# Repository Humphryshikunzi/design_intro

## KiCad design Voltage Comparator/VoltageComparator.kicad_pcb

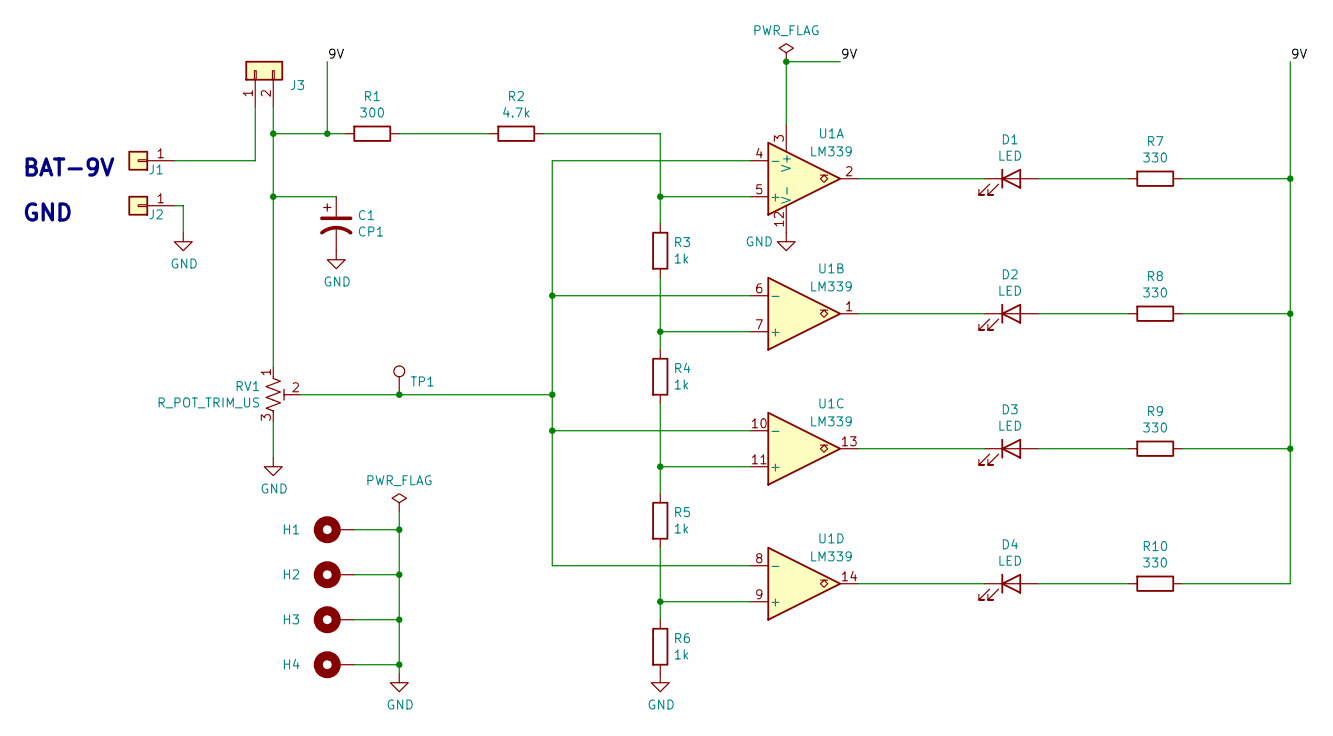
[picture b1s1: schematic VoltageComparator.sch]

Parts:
C1: CP1; CP_Radial_D10.0mm_P2.50mm
D1, D2, D3, D4: LED; LED_D3.0mm
H1, H2, H3, H4: MountingHole_Pad; MountingHole_2.5mm_Pad_TopOnly
J1, J2: Conn_01x01; SolderWire-0.1sqmm_1x01_D0.4mm_OD1mm
J3: Conn_01x02; PinHeader_1x02_P2.54mm_Vertical
R1: 300; R_Axial_DIN0207_L6.3mm_D2.5mm_P10.16mm_Horizontal
R2: 4.7k; R_Axial_DIN0207_L6.3mm_D2.5mm_P10.16mm_Horizontal
R3, R4, R5, R6: 1k; R_Axial_DIN0207_L6.3mm_D2.5mm_P10.16mm_Horizontal
R7, R8, R9, R10: 330; R_Axial_DIN0207_L6.3mm_D2.5mm_P10.16mm_Horizontal
RV1: R_POT_TRIM_US; Potentiometer_Bourns_3266P_Horizontal
TP1: TestPoint; TestPoint_Plated_Hole_D2.0mm
U1: LM339; DIP-14_W7.62mm_Socket_LongPads

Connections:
/9V: C1.1, J3.2, R1.2, R7.1, R8.1, R9.1, R10.1, RV1.1, U1.3 (V+)
GND: C1.2, H1.1, H2.1, H3.1, H4.1, J2.1, R6.2, RV1.3, U1.12 (V-)
unnamed: D1.1 (K), U1.2
unnamed: D1.2 (A), R7.2
unnamed: D2.1 (K), U1.1
unnamed: D2.2 (A), R8.2
unnamed: D3.1 (K), U1.13
unnamed: D3.2 (A), R9.2
unnamed: D4.1 (K), U1.14
unnamed: D4.2 (A), R10.2
unnamed: J1.1, J3.1
unnamed: R1.1, R2.2
unnamed: R2.1, R3.1, U1.5 (+)
unnamed: R3.2, R4.1, U1.7 (+)
unnamed: R4.2, R5.1, U1.11 (+)
unnamed: R5.2, R6.1, U1.9 (+)
unnamed: RV1.2, TP1.1, U1.4 (-), U1.6 (-), U1.8 (-), U1.10 (-)

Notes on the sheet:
BAT-9V
GND

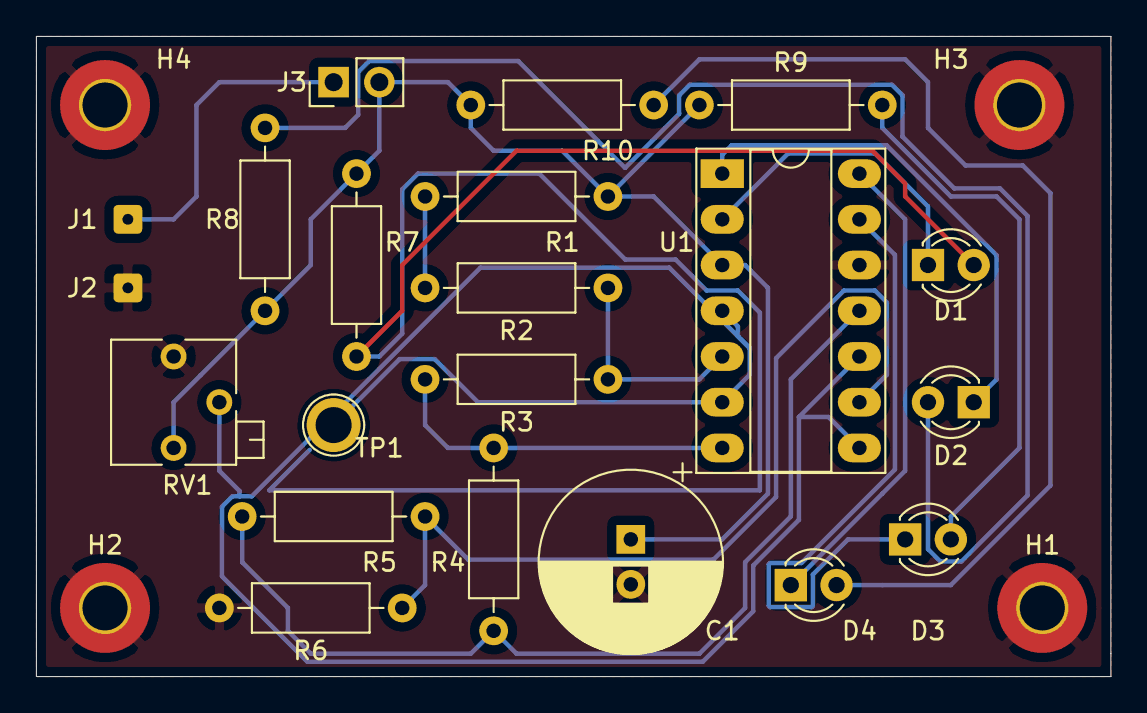
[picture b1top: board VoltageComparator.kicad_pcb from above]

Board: 2 copper layers, 59.7 x 35.6 mm, 25 parts (0 on the bottom side), 17 nets.
